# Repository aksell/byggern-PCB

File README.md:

# byggern-PCB
Board that replaces node 1 in Embedded and Industrial Computer Systems Design project at NTNU. 

The two layer board is designed using [kicad](http://kicad-pcb.org/help/getting-started/) 

## Schematic
Download pdf version [here](./pictures/schematic.pdf)

## Rendering of board

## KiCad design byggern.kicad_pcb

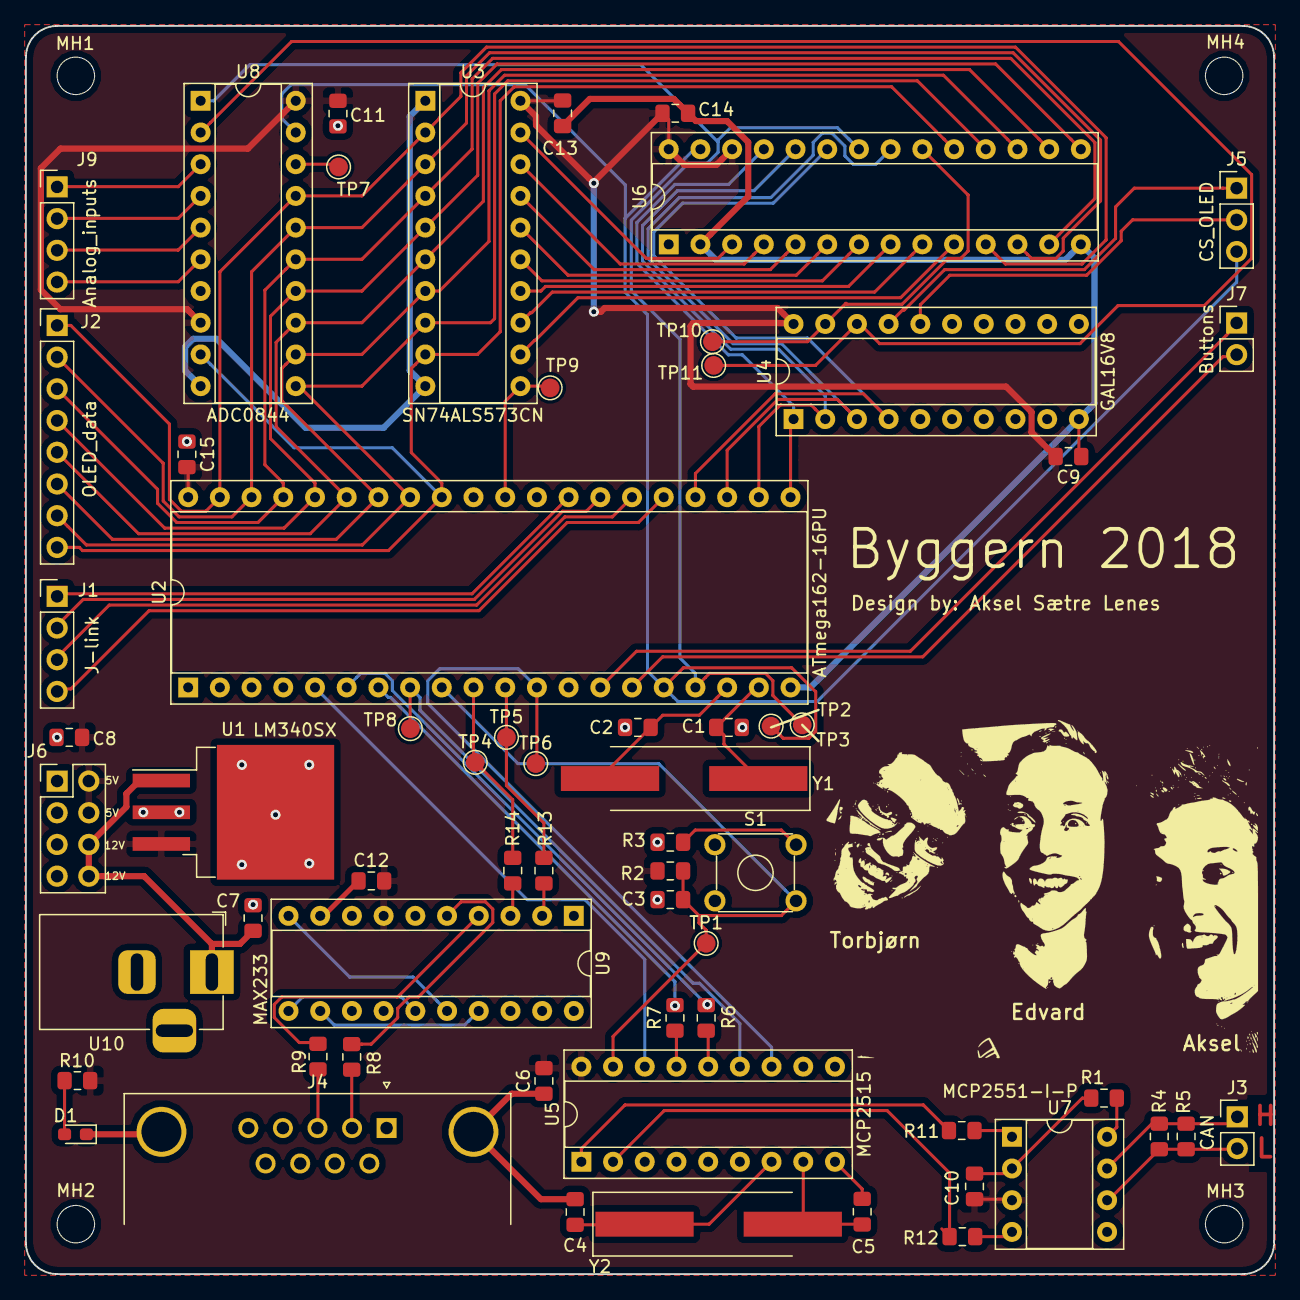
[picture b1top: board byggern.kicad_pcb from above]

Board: 2 copper layers, 100.0 x 100.0 mm, 66 parts (0 on the bottom side), 73 nets.

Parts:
C1, C2, C4, C5: 20pF; C_0805_2012Metric_Pad1.15x1.40mm_HandSolder
C3, C6, C8, C9, C10, C11, C12, C13, C14, C15: 0.1uF; C_0805_2012Metric_Pad1.15x1.40mm_HandSolder
C7: 0.22uF; C_0805_2012Metric_Pad1.15x1.40mm_HandSolder
D1: PWR_LED; LED_0603_1608Metric_Pad1.05x0.95mm_HandSolder
J1: J-link; PinHeader_1x04_P2.54mm_Vertical
J2: OLED_data; PinHeader_1x08_P2.54mm_Vertical
J3: CAN; PinHeader_1x02_P2.54mm_Vertical
J4: DB9_Female_Mounting; DSUB-9_Female_Horizontal_P2.77x2.84mm_EdgePinOffset4.94mm_H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
J5: CS_OLED; PinHeader_1x03_P2.54mm_Vertical
J6: Power_rail; PinHeader_2x04_P2.54mm_Vertical
J7: Buttons; PinHeader_1x02_P2.54mm_Vertical
J9: Analog_inputs; PinHeader_1x04_P2.54mm_Vertical
MH1, MH2, MH3, MH4: MountingHole; MountingHole_3mm
R1: 22K; R_0805_2012Metric_Pad1.15x1.40mm_HandSolder
R2: 10k; R_0805_2012Metric_Pad1.15x1.40mm_HandSolder
R3: 0.33k; R_0805_2012Metric_Pad1.15x1.40mm_HandSolder
R4, R5: 120; R_0805_2012Metric_Pad1.15x1.40mm_HandSolder
R6, R7, R8, R9, R11, R12, R13, R14: 0; R_0805_2012Metric_Pad1.15x1.40mm_HandSolder
R10: 150; R_0805_2012Metric_Pad1.15x1.40mm_HandSolder
S1: PTS645; SW_TH_Tactile_Omron_B3F-10xx
TP1, TP2, TP3, TP4, TP5, TP6, TP7, TP8, TP9, TP10, TP11: TestPoint_Pad_D1.5mm
U1: LM340SX; TO-263-3_TabPin4
U2: ATmega162-16PU; DIP-40_W15.24mm_Socket
U3: SN74ALS573CN; DIP-20_W7.62mm_Socket
U4: GAL16V8; DIP-20_W7.62mm_Socket
U5: MCP2515; DIP-18_W7.62mm_Socket
U6: IDT7164; DIP-28_W7.62mm_Socket
U7: MCP2551-I-P; DIP-8_W7.62mm_Socket
U8: ADC0844; DIP-20_W7.62mm_Socket
U9: MAX233; DIP-20_W7.62mm_Socket
U10: Barrel_jack; BarrelJack_Horizontal
Y1: 4.9MHz; Crystal_SMD_HC49-SD_HandSoldering
Y2: 16MHz; Crystal_SMD_HC49-SD_HandSoldering

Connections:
+12V: C7.1, J6.6, J6.8, U1.1, U10.1
/A0: J2.1, U2.39, U3.2, U6.11, U8.17
/A1: J2.2, U2.38, U3.3, U6.12, U8.16
/A2: J2.3, U2.37, U3.4, U6.13, U8.15
/A3: J2.4, U2.36, U3.5, U6.15, U8.14
/A4: J2.5, U2.35, U3.6, U6.16, U8.13
/A5: J2.6, U2.34, U3.7, U6.17, U8.12
/A6: J2.7, U2.33, U3.8, U6.18, U8.11
/A7: J2.8, U2.32, U3.9, U6.19, U8.9
/A8: U2.21, U4.1, U6.25
/A9: U2.22, U4.2, U6.24
/A10: U2.23, U4.3, U6.21
/A11: U2.24, U4.4, U6.23
/AL0: U3.12, U6.10
/AL1: U3.13, U6.9
/AL2: U3.14, U6.8
/AL3: U3.15, U6.7
/AL4: U3.16, U6.6
/AL5: U3.17, U6.5
/AL6: U3.18, U6.4
/AL7: U3.19, U6.3
/CAN_~INT: TP6.1, U2.12, U5.12
/LE: TP9.1, U2.30, U3.11
/MISO: R7.2, U2.7
/MOSI: R6.2, U2.6
/RXD_232: R14.2, TP4.1, U2.10
/SCK: TP8.1, U2.8, U5.13
/TXD_232: R13.2, TP5.1, U2.11
/~CS~_ADC: TP11.1, U4.18, U8.2
/~CS~_MCP: U2.5, U5.16
/~CS~_RAM: TP10.1, U4.19, U6.20
/~OE: TP3.1, U2.17, U6.22, U8.1
/~RESET: C3.1, R2.1, S1.4, TP1.1, U2.9, U5.17
/~WE: J5.3, TP2.1, U2.16, U6.27, U8.19
GND: C1.2, C2.2, C3.2, C4.2, C5.2, C6.1, C7.2, C8.2, C9.1, C10.1, C11.1, C12.1, C13.1, C14.1, C15.1, D1.1, J4.0, J4.5, J6.1, J6.3, J6.5, J6.7, R1.2, R3.1, U1.2, U1.4, U2.20, U3.1, U3.10, U4.10, U5.9, U6.2, U6.14, U7.2, U8.7, U8.10, U9.6, U9.9, U10.2, U10.3
unnamed: C1.1, U2.19, Y1.1
unnamed: C2.1, U2.18, Y1.2
unnamed: C4.1, U5.7, Y2.1
unnamed: C5.1, U5.8, Y2.2
unnamed: D1.2, R10.1
unnamed: J1.1, U2.28
unnamed: J1.2, U2.27
unnamed: J1.3, U2.26
unnamed: J1.4, U2.25
unnamed: J3.1, R4.1, R5.1, U7.7
unnamed: J3.2, R4.2, R5.2, U7.6
unnamed: J4.2, R8.1
unnamed: J4.3, R9.1
unnamed: J5.1, U4.17
unnamed: J5.2, U4.16
unnamed: J7.1, U2.14
unnamed: J7.2, U2.15
unnamed: J9.1, U8.3
unnamed: J9.2, U8.4
unnamed: J9.3, U8.5
unnamed: J9.4, U8.6
unnamed: R1.1, U7.8
unnamed: R3.2, S1.2
unnamed: R6.1, U5.14
unnamed: R7.1, U5.15
unnamed: R8.2, U9.5
unnamed: R9.2, U9.4
unnamed: R11.1, U7.1
unnamed: R11.2, U5.1
unnamed: R12.1, U7.4
unnamed: R12.2, U5.2
unnamed: R13.1, U9.2
unnamed: R14.1, U9.3
unnamed: TP7.1, U8.18
unnamed: U9.10, U9.16
unnamed: U9.11, U9.15
unnamed: U9.12, U9.17
VCC: C6.2, C8.1, C9.2, C10.2, C11.2, C12.2, C13.2, C14.2, C15.2, J6.2, J6.4, R2.2, R10.2, U1.3, U2.40, U3.20, U4.20, U5.18, U6.26, U6.28, U7.3, U8.8, U8.20, U9.7

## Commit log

2018-11-19 Add project files
2018-11-19 Add library files
2018-11-19 Add gerber and drill files
2018-11-19 Move libraries to lib folder
2018-11-19 Output fabrication files too fabrication_files directory
2018-11-19 Upload schematic and render of board
